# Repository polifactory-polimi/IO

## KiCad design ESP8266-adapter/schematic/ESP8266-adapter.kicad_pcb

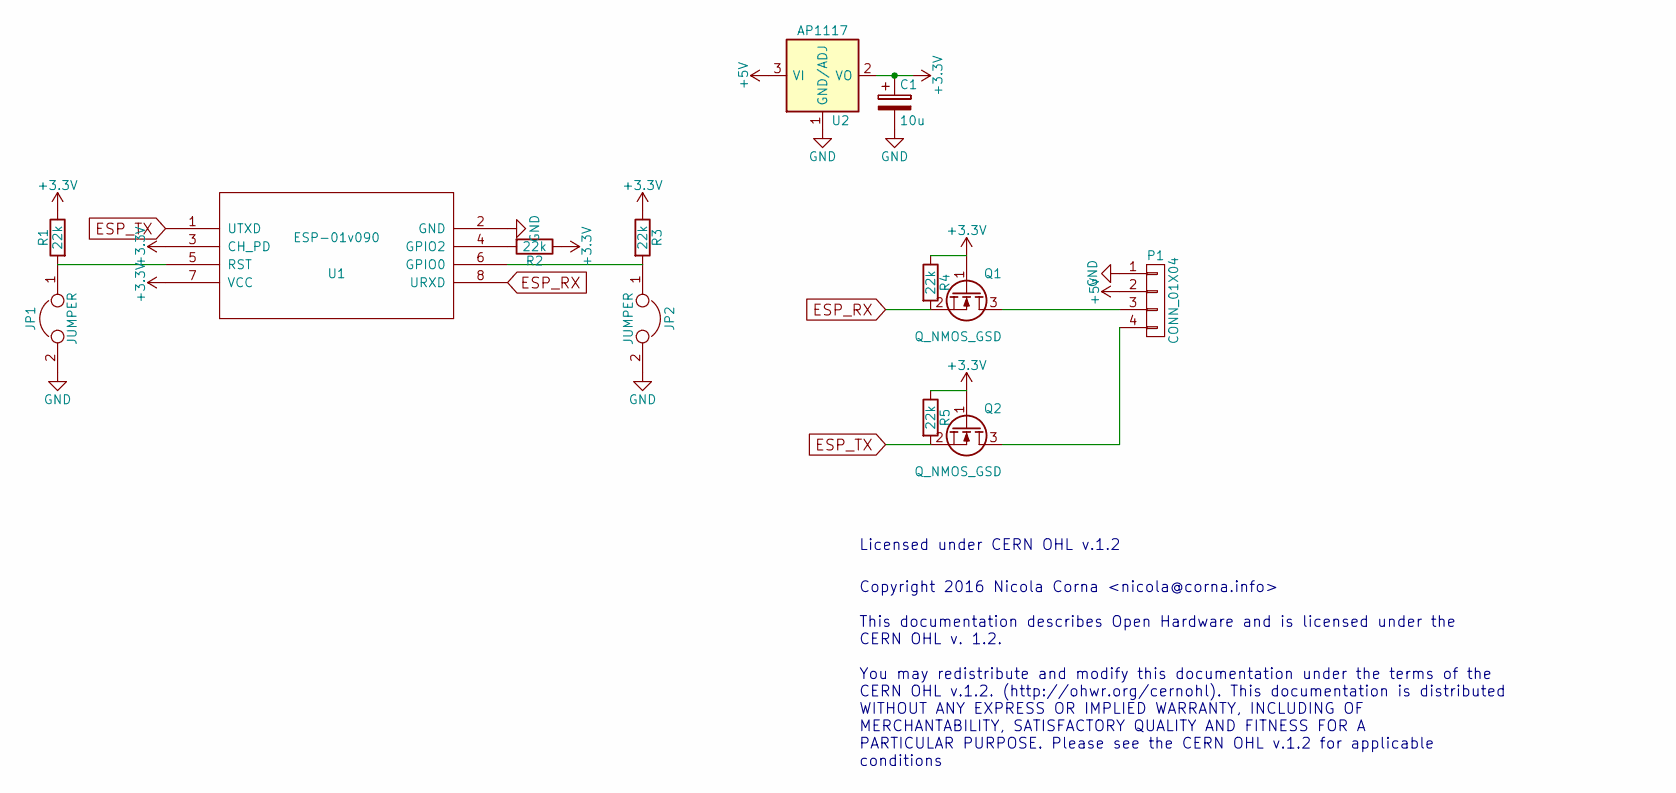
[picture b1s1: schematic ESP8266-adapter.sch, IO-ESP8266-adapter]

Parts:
C1: 10u; R_1206_HandSoldering
JP1, JP2: JUMPER; Pin_Header_Straight_1x02
P1: CONN_01X04; Pin_Header_Straight_1x04
Q1, Q2: Q_NMOS_GSD; SOT-23_Handsoldering
R1, R2, R3, R4, R5: 22k; R_1206_HandSoldering
U1: ESP-01v090; ESP-01
U2: AP1117; TO-220_Neutral123_Horizontal_LargePads

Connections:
+3V3: C1.1, Q1.1 (G), Q2.1 (G), R1.1, R2.1, R3.1, R4.1, R5.1, U1.3 (CH_PD), U1.7 (VCC), U2.2 (VO)
+5V: P1.2, U2.3 (VI)
ESP_RX: Q1.2 (S), R4.2, U1.8 (URXD)
ESP_TX: Q2.2 (S), R5.2, U1.1 (UTXD)
GND: C1.2, JP1.2, JP2.2, P1.1, U1.2 (GND), U2.1 (GND/ADJ)
unnamed: JP1.1, R1.2, U1.5 (RST)
unnamed: JP2.1, R3.2, U1.6 (GPIO0)
unnamed: P1.3, Q1.3 (D)
unnamed: P1.4, Q2.3 (D)
unnamed: R2.2, U1.4 (GPIO2)

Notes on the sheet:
Licensed under CERN OHL v.1.2
Copyright 2016 Nicola Corna <nicola@corna.info> This documentation describes Open Hardware and is licensed under the CERN OHL v. 1.2. You may redistribute and modify this documentation under the terms of the CERN OHL v.1.2. (http://ohwr.org/cernohl). This documentation is distributed WITHOUT ANY EX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

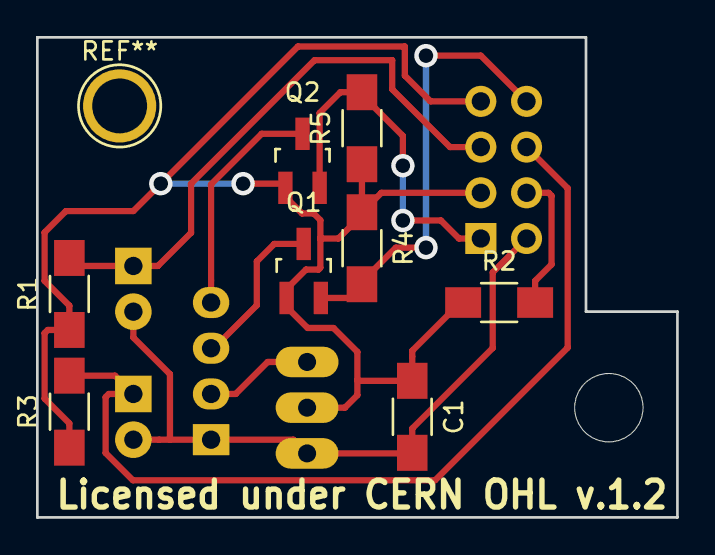
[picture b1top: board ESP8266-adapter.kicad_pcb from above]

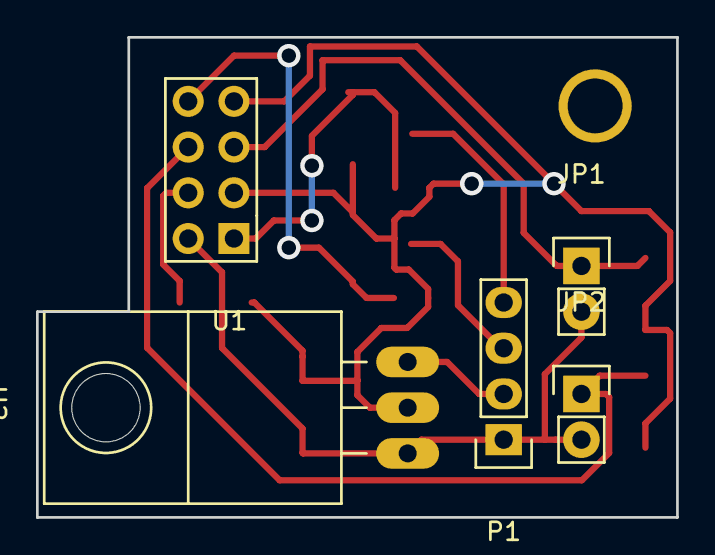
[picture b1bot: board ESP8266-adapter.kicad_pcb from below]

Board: 2 copper layers, 35.6 x 26.7 mm, 13 parts (5 on the bottom side), 10 nets.

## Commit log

2016-04-04 First commit
    Missing weather icons
2016-04-04 Remove debug Serial.print
2016-04-04 Remove weather icons
    No weather icon has been created yet
2016-05-02 Add configuration network for WiFi setup
